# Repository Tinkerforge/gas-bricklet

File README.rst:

Gas Bricklet
============

**The development of this Bricklet was stopped.**

This repository contains the firmware source code and the hardware design
files. The documentation generator configs can be found at
https://github.com/Tinkerforge/generators

Repository Content
------------------

software/:
 * examples/: Examples for all supported languages
 * build/: Makefile and compiled files
 * src/: Source code of firmware
 * generate_makefile: Shell script to generate Makefile from cmake script

hardware/:
 * Contains kicad project files and additionally schematics as pdf

datasheets/:
 * Contains datasheets for sensors and complex ICs that are used

Hardware
--------

The hardware is designed with the open source EDA Suite KiCad
(http://www.kicad.org). Before you are able to open the files,
you have to install the Tinkerforge kicad-libraries
(https://github.com/Tinkerforge/kicad-libraries). You can either clone
them directly in hardware/ or clone them in a separate folder and
symlink them into hardware/
(ln -s kicad_path/kicad-libraries project_path/hardware). After that you
can open the .pro file in hardware/ with kicad and from there view and
modify the schematics and the PCB layout.

Software
--------

If you want to do your own Brick/Bricklet firmware development we highly
recommend that you use our build environment setup script and read the
tutorial (https://www.tinkerforge.com/en/doc/Tutorials/Tutorial_Build_Environment/Tutorial.html).

To compile the C code we recommend you to install the newest GNU Arm Embedded
Toolchain (https://launchpad.net/gcc-arm-embedded/+download).
You also need to install bricklib2 (https://github.com/Tinkerforge/bricklib2).

You can either clone it directly in software/src/ or clone it in a
separate folder and symlink it into software/src/
(ln -s bricklib_path/bricklib2 project_path/software/src/). Finally make sure to
have CMake installed (http://www.cmake.org/cmake/resources/software.html).

After that you can generate a Makefile from the cmake script with the
generate_makefile shell script (in software/) and build the firmware
by invoking make in software/build/. The firmware (.zbin) can then be found
in software/build/ and uploaded with brickv (click button "Flashing"
on start screen).

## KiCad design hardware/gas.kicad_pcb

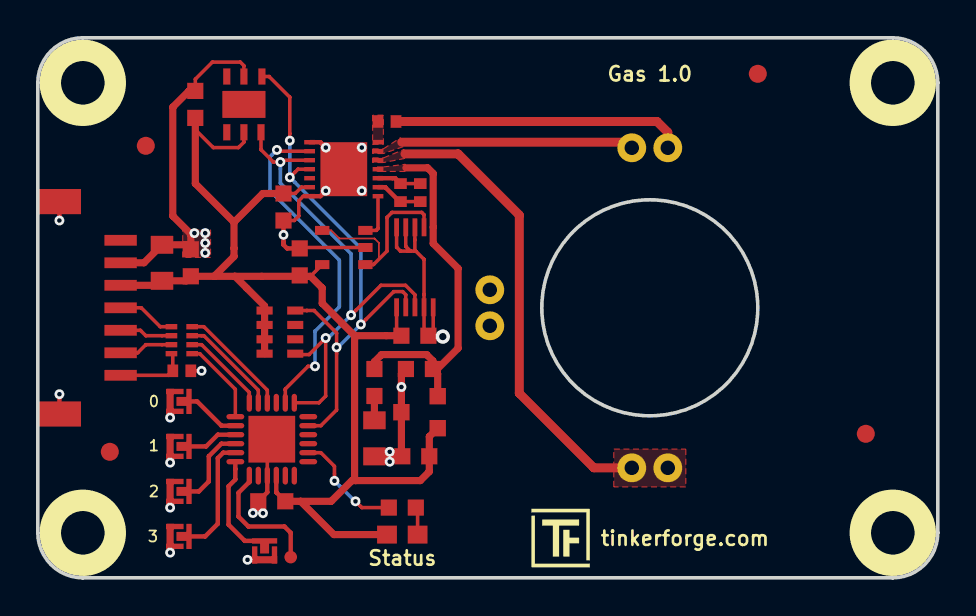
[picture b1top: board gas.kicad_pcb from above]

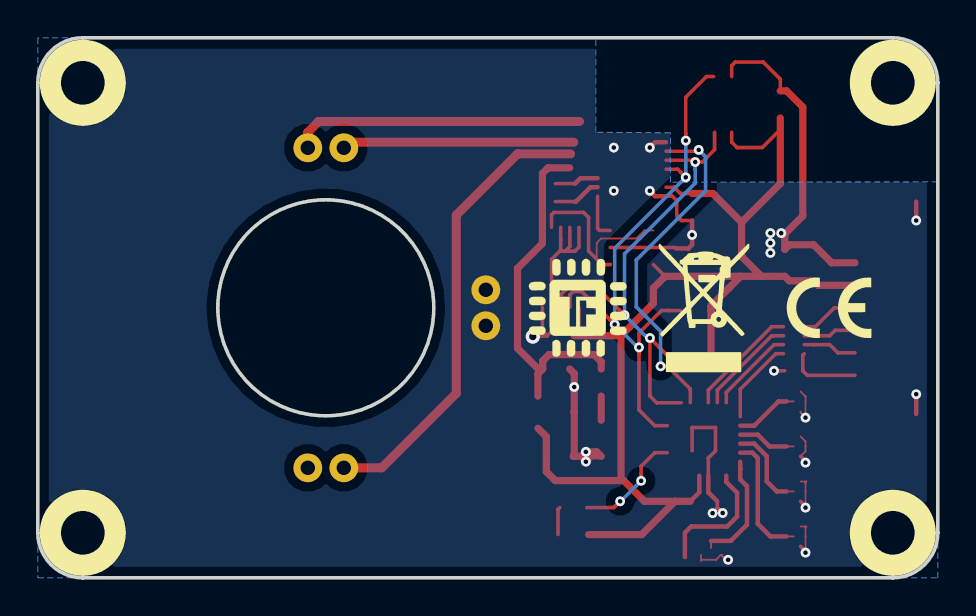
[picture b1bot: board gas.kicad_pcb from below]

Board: 2 copper layers, 50.0 x 30.0 mm, 43 parts (2 on the bottom side), 31 nets.

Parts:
C1: 220pF; C0402F
C2: 10uF; C0805
C3: 1uF; C0603F
C4, C5, C6, C7, C10, C11, C12: 100nF; C0603F
C8: 10uF TPSA106K010R0900; C0805P
C9: DNP; R0402F
D1: blue; D0603E
Fiducial_Mark: VAL**; Fiducial_Mark
Fiducial_Mark#2, Fiducial_Mark#3, Fiducial_Mark#4: VAL**; Fiducial_Mark
P1: CON-SENSOR2
P2: DEBUG; DEBUG_PAD
P3: BOOT; SolderJumper
P7: 0; SolderJumper
P8: 1; SolderJumper
P9: 2; SolderJumper
P10: 3; SolderJumper
R1, R2: 1k; R0603F
R3: 499k; R0402F
R4: 49,9; R0402F
RP1: 82; 4X0402
RP2: 10k; 0603X4
U1: XMC1300; QFN24-4x4mm-0.5mm
U2, U3, U4, U5: DRILL; DRILL_NP
U6: HDC1080; DFN6-30x30_humidity
U7: ISL60002; SOT23-3
U8: LMP91000; WSON-14-LMP91000
U9: MCP6041; SOT23-5
U10: MCP3423; MSOP10-0.5
U11: spec-sensor
VAL: WEEE_7mm
VAL#2: CE_5mm

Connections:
Enable: U1.20, U8.2
GND: C1.2, C2.1, C3.1, C4.2, C5.2, C6.2, C7.2, C8.2, C10.2, C11.2, C12.2, P1.2, P1.EP, P3.1, P7.1, P8.1, P9.1, P10.1, U1.9, U1.EXP, U6.2, U7.3, U8.1, U8.7, U8.15, U9.2, U10.3, U10.4, U10.5, U10.9, U10.10, U11.2, U11.3
unnamed: C1.1, P1.7, RP1.4
unnamed: C6.1, R2.2, U7.2, U8.11, U10.1
unnamed: C8.1, R2.1
unnamed: C9.1, R3.1, U8.10
unnamed: C9.2, R3.2, U8.9
unnamed: D1.2, R1.2
unnamed: P1.4, RP1.1
unnamed: P1.5, RP1.2
unnamed: P1.6, RP1.3
unnamed: P2.1, U1.7
unnamed: P3.2, U1.6
unnamed: R1.1, U1.14
unnamed: R4.1, U11.5
unnamed: R4.2, U8.14
unnamed: U8.8, U9.3
unnamed: U9.1, U9.4, U10.2
unnamed: U8.12, U11.1, U11.6
unnamed: U8.13, U11.4
S-CLK: RP1.7, U1.23
S-CS: RP1.8, U1.22
S-MISO: RP1.5, U1.1
S-MOSI: RP1.6, U1.24
SCL0: RP2.5, U1.19, U6.6, U8.3, U10.8
SDA0: RP2.8, U1.17, U6.1, U8.4, U10.7
SolderJumper0: P7.2, U1.2
SolderJumper1: P8.2, U1.3
SolderJumper2: P9.2, U1.4
SolderJumper3: P10.2, U1.5
VCC: C2.2, C3.2, C4.1, C5.1, C7.1, C10.1, C11.1, C12.1, D1.1, P1.3, RP2.1, RP2.2, RP2.3, RP2.4, U1.10, U6.5, U7.1, U8.6, U9.5, U10.6

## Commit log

2019-02-06 added datasheet
2019-02-06 added .gitignore and readme
2019-02-06 added gitignore
2019-02-06 added schematic
2019-02-06 added pcb design
2019-02-07 pcb design
2019-02-07 final pcb design
2019-02-07 add sym table
2019-02-07 added fiducial marks
2019-03-20 changed mcu to xmc 1300, new pcb design,
2019-03-20 changed to xmc1300, new pcb design for part clearance, added smd M3 spacer
2019-03-21 updated M3 spacer footprint, drc check
2019-03-21 changed status led placement, plotted gerber files
2019-04-09 Fix USIC ch0/1 comment
2019-04-09 changed debugpin
2019-05-03 new design
2019-05-29 all new design
2019-05-29 changes in pcb design
2019-06-03 final prototype
2019-08-14 Add hdc1080 datasheet
2019-08-15 corrected wrong pinout of ISL60002 in schematic and pcb design
2019-08-15 drc check
2019-08-26 add fiducials
2019-09-13 Remove unused pdf, add lmp91000 datasheet
2019-09-18 Add MC3423 datasheet
2019-09-18 Add firmware
2019-09-18 Add tests
2019-09-18 Add missing line breaks in logging
2019-09-18 Add temperature and humidity offset to calibration
2019-09-18 Remove gas type from calibration (set pyhsically on the PCB)
2019-09-18 Add gas type detection support
    This is done through solder jumpers on the PCB.
2019-09-26 Fix typo
2019-09-26 Use inverse ADC value.
    VOUT of LMP91000 is connected to "-" of MCP3423.
    Thus an increase of VOUT will result in a decreased ADC count.
2019-09-27 Add isl600002, mcp6041 and relevant spec datasheets
2019-12-02 Mark development as stopped
2021-10-25 Update KiCad link
    https://www.kicad.org/blog/2021/10/Avoid-links-to-former-kicad-domain/
2022-07-06 Add license files.
2025-10-04 Fix compatibility with new Docker build image (GCC 14.2.1)
